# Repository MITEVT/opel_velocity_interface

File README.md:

# Opel GT Driver Interface Module

MIT EVT's Opel GT Project Driver Interface Module. Acts as an inteface between the user and the electrical system for controlling power distribution and auxiliary peripherals.
	
## Target
NXP LPC11C14 Cortex-M0 Microcontroller

## Description
Takes user input in the form of key switches, level toggles, and button presses to activate main power distribution system and control auxilairy peripherals such as lights.

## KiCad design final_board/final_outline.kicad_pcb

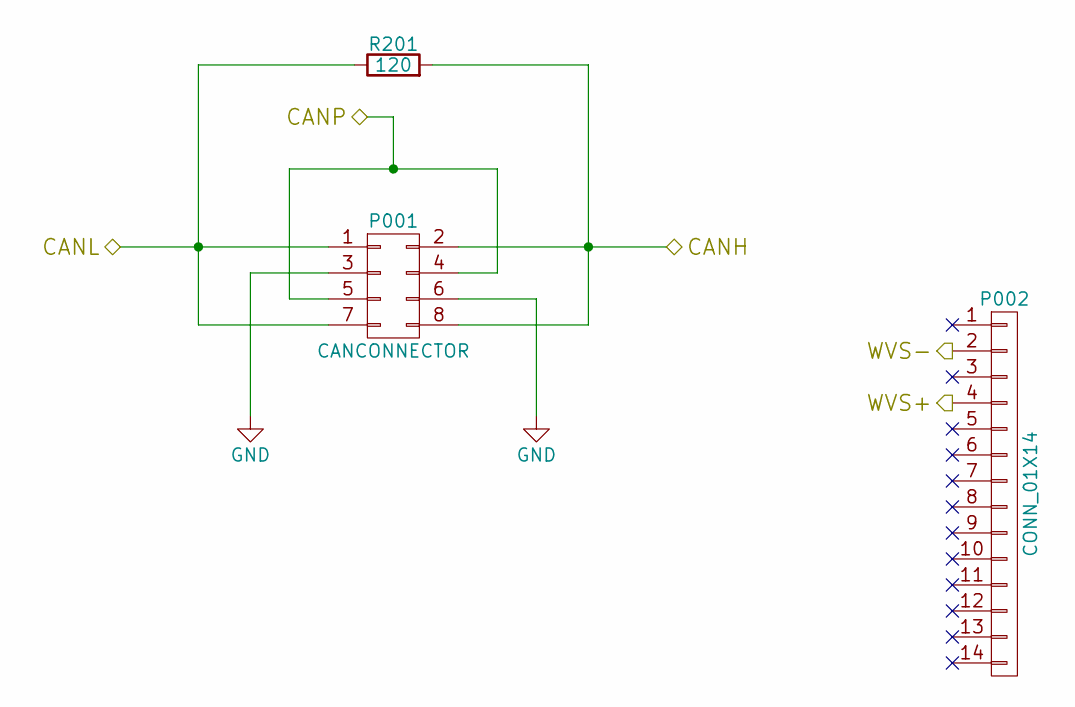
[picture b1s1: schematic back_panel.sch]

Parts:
P001: CANCONNECTOR; 776280-1
P002: CONN_01X14; 776267-1
R201: 120; R_0603_HandSoldering

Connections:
+12V: P001.4, P001.5; also elsewhere on the board
/BACK_PANEL/CANH: P001.2, P001.8, R201.2; also elsewhere on the board
/BACK_PANEL/CANL: P001.1, P001.7, R201.1; also elsewhere on the board
/BACK_PANEL/WVS+: P002.4; also elsewhere on the board
/BACK_PANEL/WVS-: P002.2; also elsewhere on the board
GND: P001.3, P001.6; also elsewhere on the board

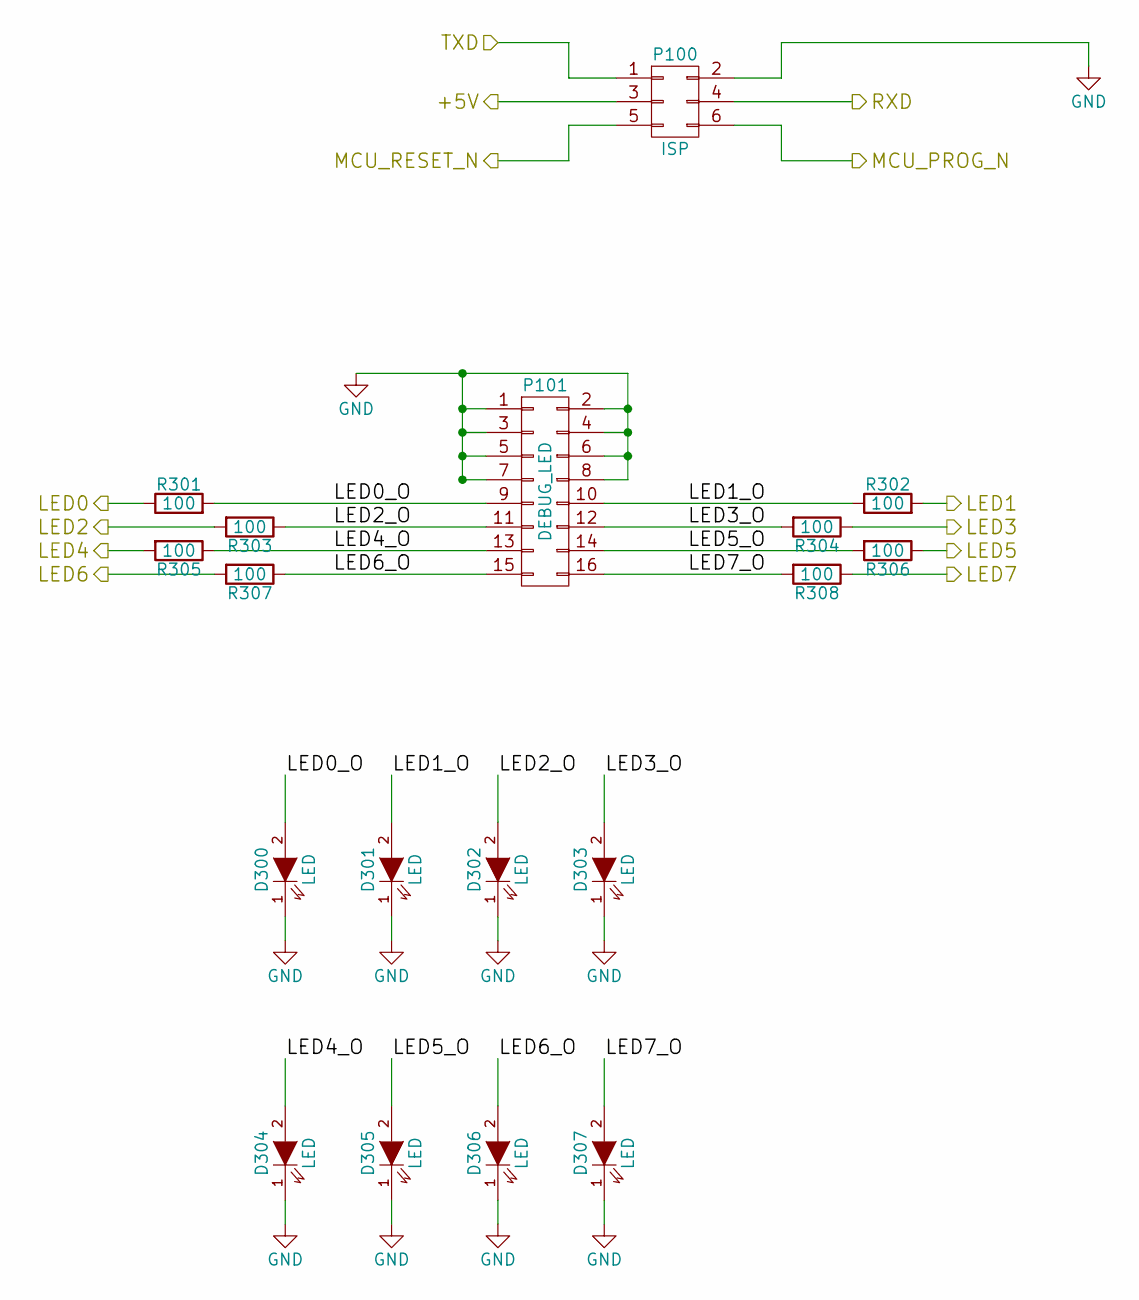
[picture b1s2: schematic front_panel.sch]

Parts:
D300, D301, D302, D303, D304, D305, D306, D307: LED; LED_0805
P100: ISP; Molex_Microfit3_Header_02x03_Angled_43045-060x
P101: DEBUG_LED; Molex_Microfit3_Header_02x08_Angled_43045-160x
R301, R302, R303, R304, R305, R306, R307, R308: 100; R_0603_HandSoldering

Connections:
+5V: P100.3; also elsewhere on the board
/FRONT_PANEL/LED0: R301.1; also elsewhere on the board
/FRONT_PANEL/LED0_O: D300.2 (A), P101.9, R301.2
/FRONT_PANEL/LED1: R302.2; also elsewhere on the board
/FRONT_PANEL/LED1_O: D301.2 (A), P101.10, R302.1
/FRONT_PANEL/LED2: R303.2; also elsewhere on the board
/FRONT_PANEL/LED2_O: D302.2 (A), P101.11, R303.1
/FRONT_PANEL/LED3: R304.1; also elsewhere on the board
/FRONT_PANEL/LED3_O: D303.2 (A), P101.12, R304.2
/FRONT_PANEL/LED4: R305.2; also elsewhere on the board
/FRONT_PANEL/LED4_O: D304.2 (A), P101.13, R305.1
/FRONT_PANEL/LED5: R306.1; also elsewhere on the board
/FRONT_PANEL/LED5_O: D305.2 (A), P101.14, R306.2
/FRONT_PANEL/LED6: R307.2; also elsewhere on the board
/FRONT_PANEL/LED6_O: D306.2 (A), P101.15, R307.1
/FRONT_PANEL/LED7: R308.1; also elsewhere on the board
/FRONT_PANEL/LED7_O: D307.2 (A), P101.16, R308.2
/FRONT_PANEL/MCU_PROG_N: P100.6; also elsewhere on the board
/FRONT_PANEL/MCU_RESET_N: P100.5; also elsewhere on the board
/FRONT_PANEL/RXD: P100.4; also elsewhere on the board
/FRONT_PANEL/TXD: P100.1; also elsewhere on the board
GND: D300.1 (K), D301.1 (K), D302.1 (K), D303.1 (K), D304.1 (K), D305.1 (K), D306.1 (K), D307.1 (K), P100.2, P101.1, P101.2, P101.3, P101.4, P101.5, P101.6, P101.7, P101.8; also elsewhere on the board

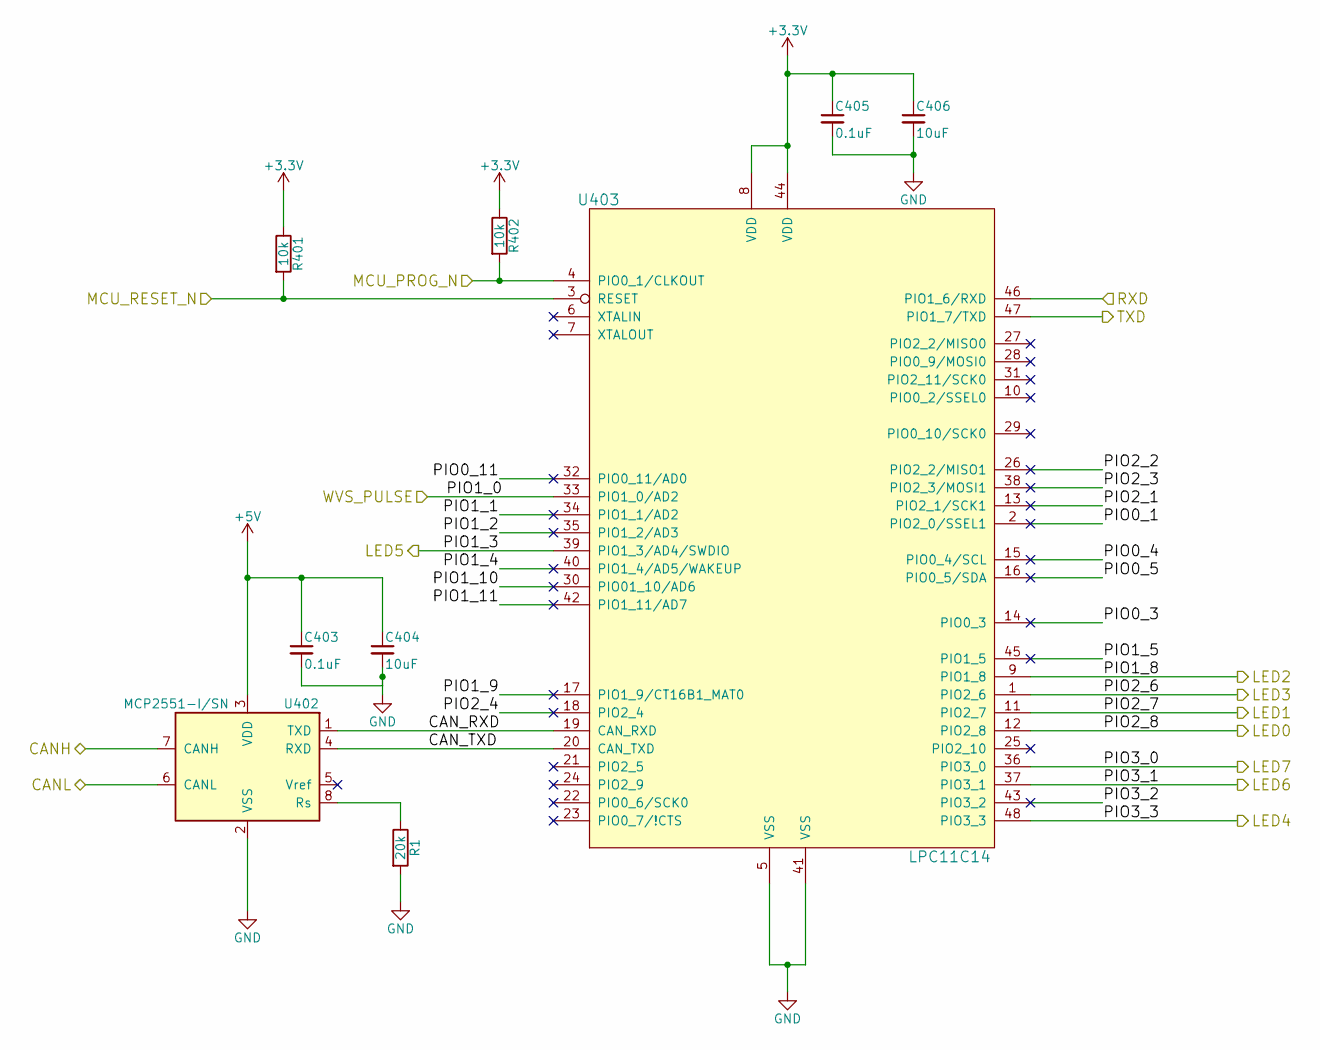
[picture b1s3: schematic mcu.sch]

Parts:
C403, C405: 0.1uF; C_0603_HandSoldering
C404, C406: 10uF; C_0805_HandSoldering
R1: 20k; C_0603_HandSoldering
R401, R402: 10k; R_0603_HandSoldering
U402: MCP2551-I/SN; SOIC-8_3.9x4.9mm_Pitch1.27mm
U403: LPC11C14; LQFP-48_7x7mm_Pitch0.5mm

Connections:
+3V3: C405.1, C406.1, R401.1, R402.1, U403.8 (VDD), U403.44 (VDD); also elsewhere on the board
+5V: C403.1, C404.1, U402.3 (VDD); also elsewhere on the board
/BACK_PANEL/CANH: U402.7 (CANH); also elsewhere on the board
/BACK_PANEL/CANL: U402.6 (CANL); also elsewhere on the board
/FRONT_PANEL/LED0: U403.12 (PIO2_8); also elsewhere on the board
/FRONT_PANEL/LED1: U403.11 (PIO2_7); also elsewhere on the board
/FRONT_PANEL/LED2: U403.9 (PIO1_8); also elsewhere on the board
/FRONT_PANEL/LED3: U403.1 (PIO2_6); also elsewhere on the board
/FRONT_PANEL/LED4: U403.48 (PIO3_3); also elsewhere on the board
/FRONT_PANEL/LED5: U403.39 (PIO1_3/AD4/SWDIO); also elsewhere on the board
/FRONT_PANEL/LED6: U403.37 (PIO3_1); also elsewhere on the board
/FRONT_PANEL/LED7: U403.36 (PIO3_0); also elsewhere on the board
/FRONT_PANEL/MCU_PROG_N: R402.2, U403.4 (PIO0_1/CLKOUT); also elsewhere on the board
/FRONT_PANEL/MCU_RESET_N: R401.2, U403.3 (RESET); also elsewhere on the board
/FRONT_PANEL/RXD: U403.46 (PIO1_6/RXD); also elsewhere on the board
/FRONT_PANEL/TXD: U403.47 (PIO1_7/TXD); also elsewhere on the board
/Micro_Controller/PIO0_1: U403.2 (PIO2_0/SSEL1)
/Micro_Controller/PIO0_3: U403.14 (PIO0_3)
/Micro_Controller/PIO0_4: U403.15 (PIO0_4/SCL)
/Micro_Controller/PIO0_5: U403.16 (PIO0_5/SDA)
/Micro_Controller/PIO0_11: U403.32 (PIO0_11/AD0)
/Micro_Controller/PIO1_1: U403.34 (PIO1_1/AD2)
/Micro_Controller/PIO1_2: U403.35 (PIO1_2/AD3)
/Micro_Controller/PIO1_4: U403.40 (PIO1_4/AD5/WAKEUP)
/Micro_Controller/PIO1_5: U403.45 (PIO1_5)
/Micro_Controller/PIO1_9: U403.17 (PIO1_9/CT16B1_MAT0)
/Micro_Controller/PIO1_10: U403.30 (PIO01_10/AD6)
/Micro_Controller/PIO1_11: U403.42 (PIO1_11/AD7)
/Micro_Controller/PIO2_1: U403.13 (PIO2_1/SCK1)
/Micro_Controller/PIO2_2: U403.26 (PIO2_2/MISO1)
/Micro_Controller/PIO2_3: U403.38 (PIO2_3/MOSI1)
/Micro_Controller/PIO2_4: U403.18 (PIO2_4)
/Micro_Controller/PIO3_2: U403.43 (PIO3_2)
/Micro_Controller/WVS_PULSE: U403.33 (PIO1_0/AD2); also elsewhere on the board
GND: C403.2, C404.2, C405.2, C406.2, R1.2, U402.2 (VSS), U403.5 (VSS), U403.41 (VSS); also elsewhere on the board
unnamed: R1.1, U402.8 (Rs)

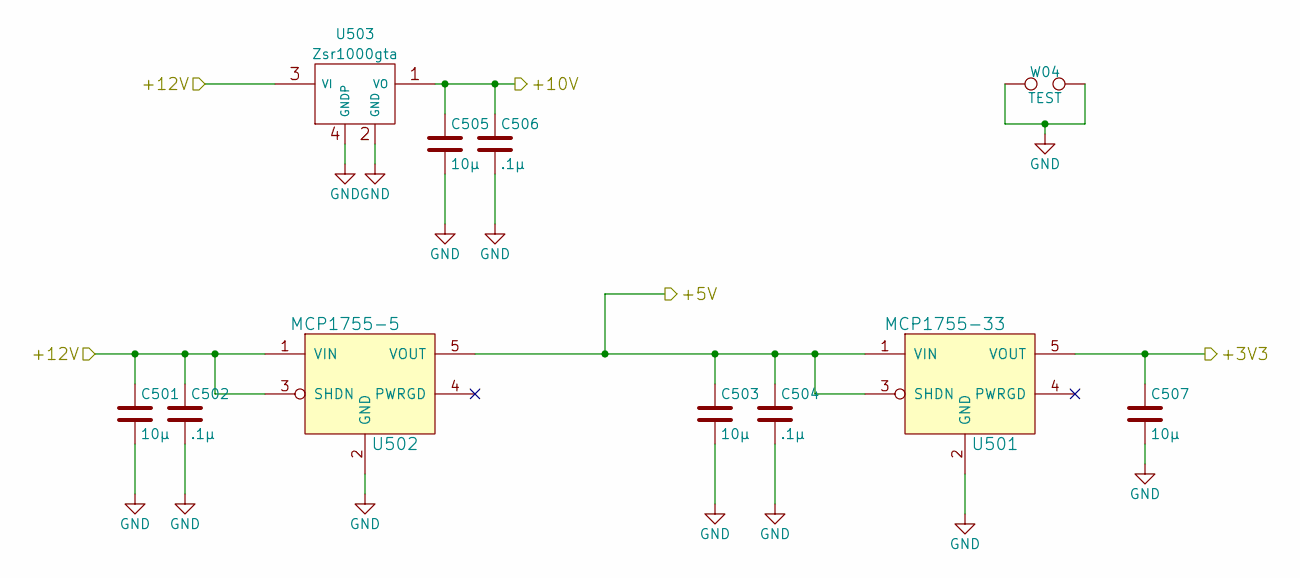
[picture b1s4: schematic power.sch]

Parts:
C501, C503, C505, C507: 10μ; C_0805_HandSoldering
C502, C504, C506: .1μ; C_0603_HandSoldering
U501: MCP1755-33; SOT-23-5
U502: MCP1755-5; SOT-23-5
U503: Zsr1000gta; SOT-223
W04: TEST; Test_Point_2Pads

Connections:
+3V3: C507.1, U501.5 (VOUT); also elsewhere on the board
+5V: C503.1, C504.1, U501.1 (VIN), U501.3 (SHDN), U502.5 (VOUT); also elsewhere on the board
+12V: C501.1, C502.1, U502.1 (VIN), U502.3 (SHDN), U503.3 (VI); also elsewhere on the board
GND: C501.2, C502.2, C503.2, C504.2, C505.2, C506.2, C507.2, U501.2 (GND), U502.2 (GND), U503.2 (GND), U503.4 (GNDP), W04.1, W04.2; also elsewhere on the board
VCC: C505.1, C506.1, U503.1 (VO); also elsewhere on the board

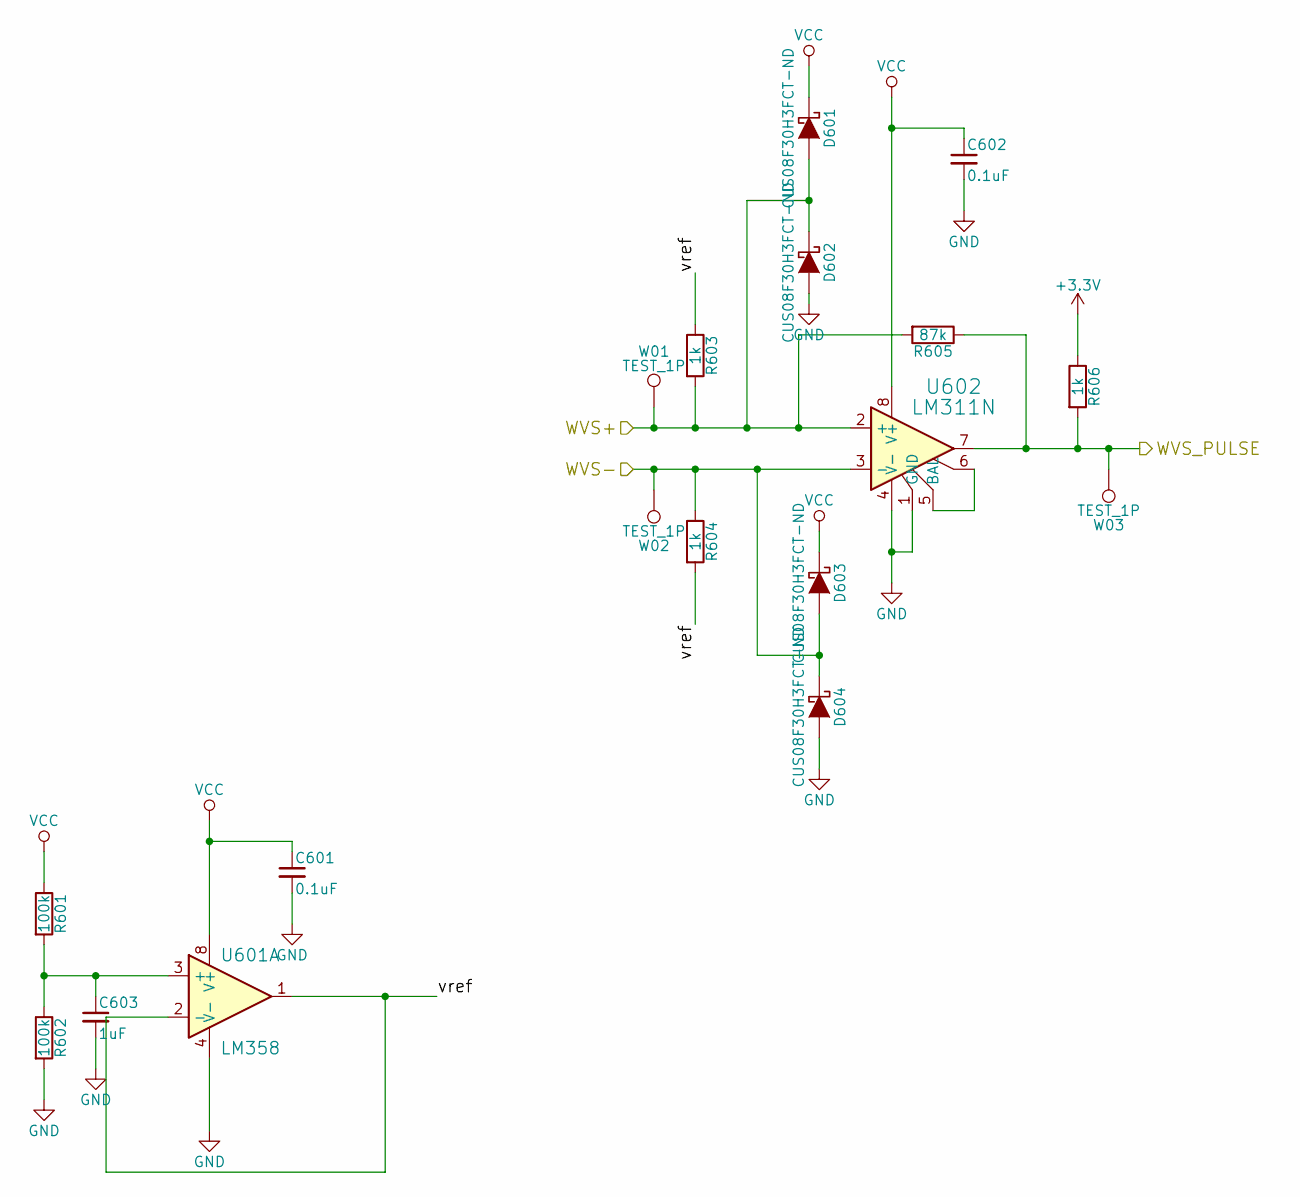
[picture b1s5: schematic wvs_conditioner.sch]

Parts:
C601, C602: 0.1uF; C_0603_HandSoldering
C603: 1uF; C_0603_HandSoldering
D601, D602, D603, D604: CUS08F30H3FCT-ND; SOD-323
R601, R602: 100k; R_0603_HandSoldering
R603, R604, R606: 1k; R_0603_HandSoldering
R605: 87k; R_0603_HandSoldering
U601: LM358; SOIC-8_3.9x4.9mm_Pitch1.27mm
U602: LM311N; SOIC-8_3.9x4.9mm_Pitch1.27mm
W01, W02, W03: TEST_1P; smd_test_pad

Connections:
+3V3: R606.1; also elsewhere on the board
/BACK_PANEL/WVS+: D601.2 (A), D602.1 (K), R603.2, R605.2, U602.2 (+), W01.1; also elsewhere on the board
/BACK_PANEL/WVS-: D603.2 (A), D604.1 (K), R604.1, U602.3 (-), W02.1; also elsewhere on the board
/Micro_Controller/WVS_PULSE: R605.1, R606.2, U602.7, W03.1; also elsewhere on the board
/WVS_Conditioner/vref: R603.1, R604.2, U601.1, U601.2 (-)
GND: C601.2, C602.2, C603.2, D602.2 (A), D604.2 (A), R602.2, U601.4 (V-), U602.1 (GND), U602.4 (V-); also elsewhere on the board
unnamed: C603.1, R601.2, R602.1, U601.3 (+)
unnamed: U602.5 (BAL), U602.6
VCC: C601.1, C602.1, D601.1 (K), D603.1 (K), R601.1, U601.8 (V+), U602.8 (V+); also elsewhere on the board

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
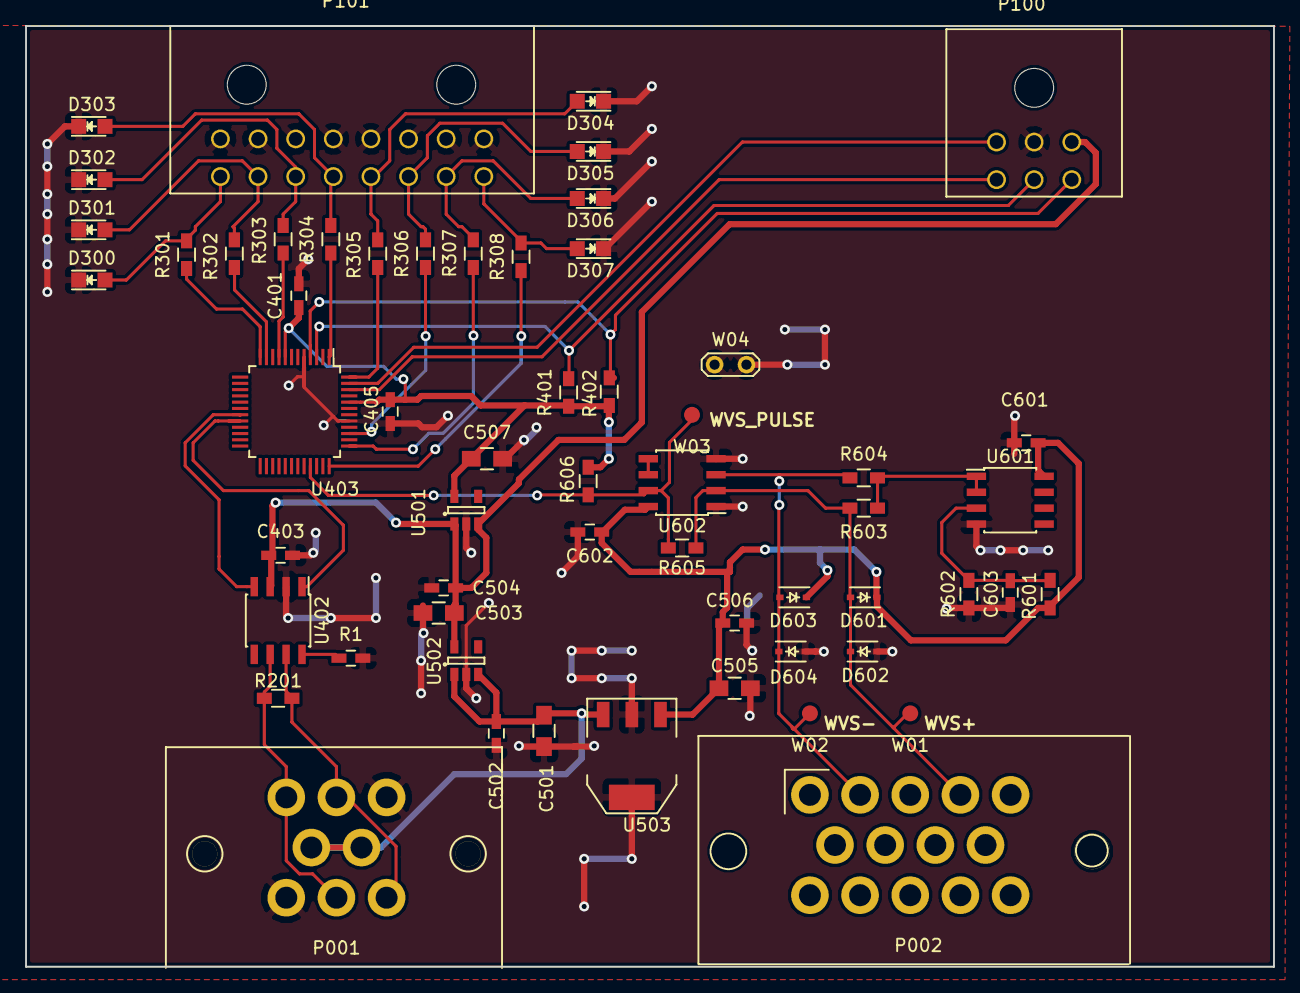
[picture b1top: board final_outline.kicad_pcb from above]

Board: 2 copper layers, 99.5 x 75.0 mm, 58 parts (0 on the bottom side), 36 nets.

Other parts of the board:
C401: 0.1uF; C_0603_HandSoldering

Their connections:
+3V3: C401.1; also elsewhere on the board
GND: C401.2; also elsewhere on the board

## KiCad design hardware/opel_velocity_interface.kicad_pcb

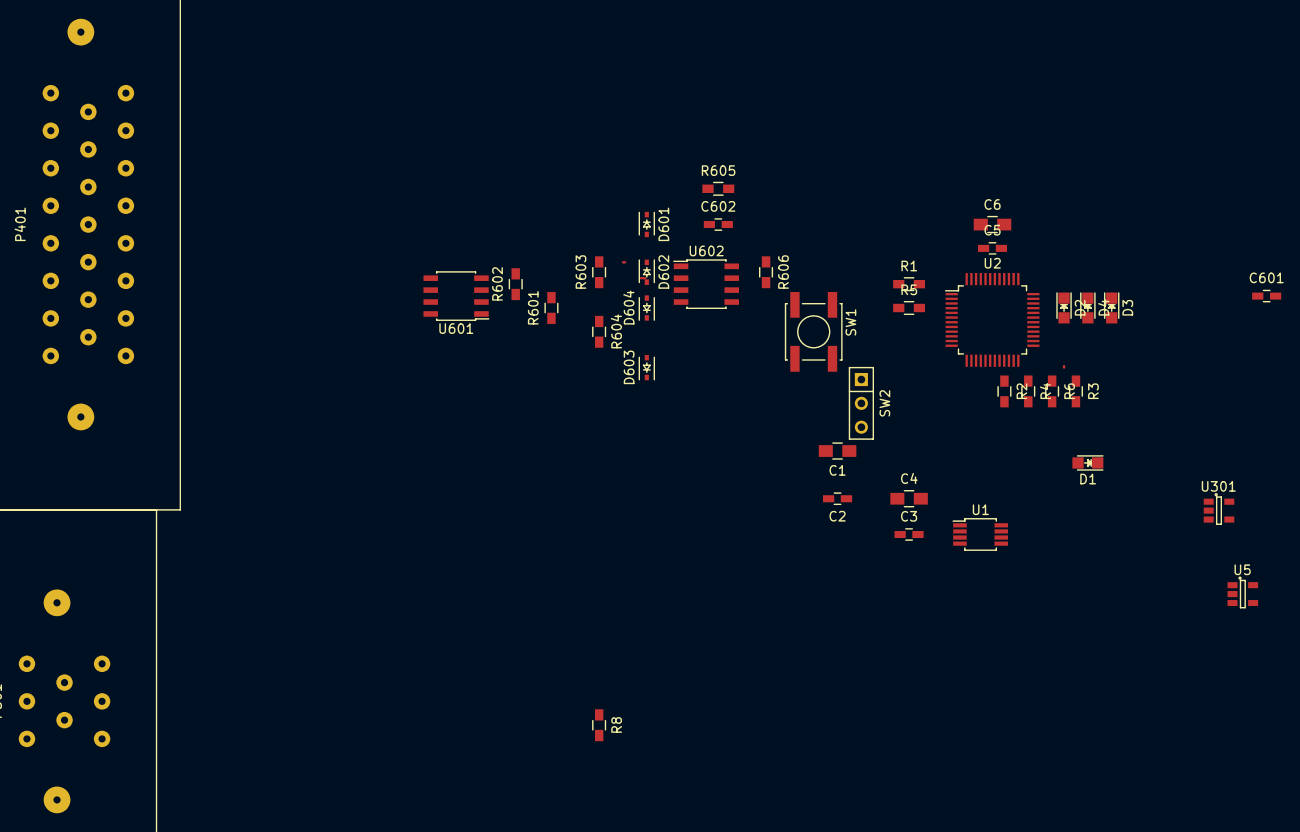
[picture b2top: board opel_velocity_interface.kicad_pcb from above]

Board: 2 copper layers, 39 parts (0 on the bottom side), 25 nets.

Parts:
C1, C4: 1uF; C_0805_HandSoldering
C2, C3, C5, C601, C602: 0.1uF; C_0603_HandSoldering
C6: 1=uF; C_0805_HandSoldering
D1, D2, D3, D4: LED; LED-0805
D601, D602, D603, D604: CUS08F30H3FTR-ND; SOD-323
P401: CONN_01X23; 1-776087-2
P501: CONN_01X08; 1-776280-2
R1, R5, R606: 10k; R_0603_HandSoldering
R2, R3, R4, R6: 100; R_0603_HandSoldering
R8: 120; R_0603_HandSoldering
R601, R602, R603, R604: 1k; R_0603_HandSoldering
R605: 87k; R_0603_HandSoldering
SW1: SPST; SW_SPST_EVPBF
SW2: SPST; SW_Micro_SPST
U1: ISO1050; MSOP-8_3x3mm_Pitch0.65mm
U2: LPC11C14; LQFP-48_7x7mm_Pitch0.5mm
U5, U301: MCP1755; SOT-23-5
U601: LM358; SOIC-8_3.9x4.9mm_Pitch1.27mm
U602: LM311N; SOIC-8_3.9x4.9mm_Pitch1.27mm

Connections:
+3V3: C3.1, C4.1, C5.1, C6.1, R1.1, R5.1, R606.1, U1.1, U2.8, U2.44, U5.5
+12V: C601.1, C602.1, D601.1, D603.1, P401.18, R601.1, U5.1, U5.3, U301.1, U301.3, U601.8, U602.8
/Input Connectors/MCU_PROG_N: P401.22, R5.2, SW2.1, U2.4
/Input Connectors/MCU_RESET_N: P401.21, R1.2, SW1.1, U2.3
/Input Connectors/RXD: P401.19, U2.46
/Input Connectors/TXD: P401.20, U2.47
/Input Connectors/WVS+: D601.2, D602.1, R603.2, R605.1, U602.2
/Input Connectors/WVS-: D603.2, D604.1, R604.1, U602.3
/Micro Controller/CAN1H: P501.2, R8.1, U1.7
/Micro Controller/CAN1L: P501.3, R8.2, U1.6
/Micro Controller/CAN1P: C1.1, C2.1, P501.1, U1.8
/Micro Controller/WVS_PULSE: R605.2, R606.2, U2.45, U602.7
/WVS_Conditioner/vref: R603.1, R604.2, U601.1, U601.2
GND: C1.2, C2.2, C3.2, C4.2, C5.2, C6.2, C601.2, C602.2, D1.1, D2.1, D3.1, D4.1, D602.2, D604.2, P401.23, P501.4, R602.2, SW1.2, SW2.2, U1.4, U2.5, U2.41, U5.2, U601.4, U602.4, U602.6
unnamed: D1.2, R2.2
unnamed: D2.2, R3.2
unnamed: D3.2, R4.2
unnamed: D4.2, R6.2
unnamed: R2.1, U2.21
unnamed: R3.1, U2.24
unnamed: R4.1, U2.22
unnamed: R6.1, U2.23
unnamed: R601.2, R602.1, U601.3
unnamed: U1.2, U2.19
unnamed: U1.3, U2.20

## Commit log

2015-10-24 First draft of WVS schematic
2015-10-24 update gitignore
2015-10-24 small merging of helmuts example
2015-10-25 wheel velocity
2015-10-31 fixed git ignore
2015-10-31 Works for transmitting, some formatting corrections
2015-10-31 Recieves and transmits two inputs
2015-10-31 Back to only one sensor
2016-01-09 Fixed some formatting and made slight readability changes
2016-01-09 some changes including to method of timing 1/5 seconds
2016-01-09 velocity sensor added
2016-01-09 wheel velocity sensor circuit added
2016-01-09 Changed CAN Chip, added capacitors, added reference
2016-01-09 Final changes to board
2016-01-11 Fixed issue with referencing /home/helmuth/zsr1000gta
2016-01-13 Fixed some routing
2016-01-13 The ISP is no longer providing 12 volts
2016-01-13 Removed useless trace
2016-01-13 Fixed planes
2016-01-13 Panelized version
2016-01-13 Added backup files to gitignore
2016-01-14 Resistor values changed from 1k to 100k
2016-09-17 Added ground via
2016-11-13 Updated PCB by replacing old parts, fixing voltage regulator, adding test points, and general improvements
2017-01-14 Velocity module for test bench that sends some data
2017-02-18 Sends CAN heartbeat and receives all messages
2017-03-04 Updates to test bench configuration
